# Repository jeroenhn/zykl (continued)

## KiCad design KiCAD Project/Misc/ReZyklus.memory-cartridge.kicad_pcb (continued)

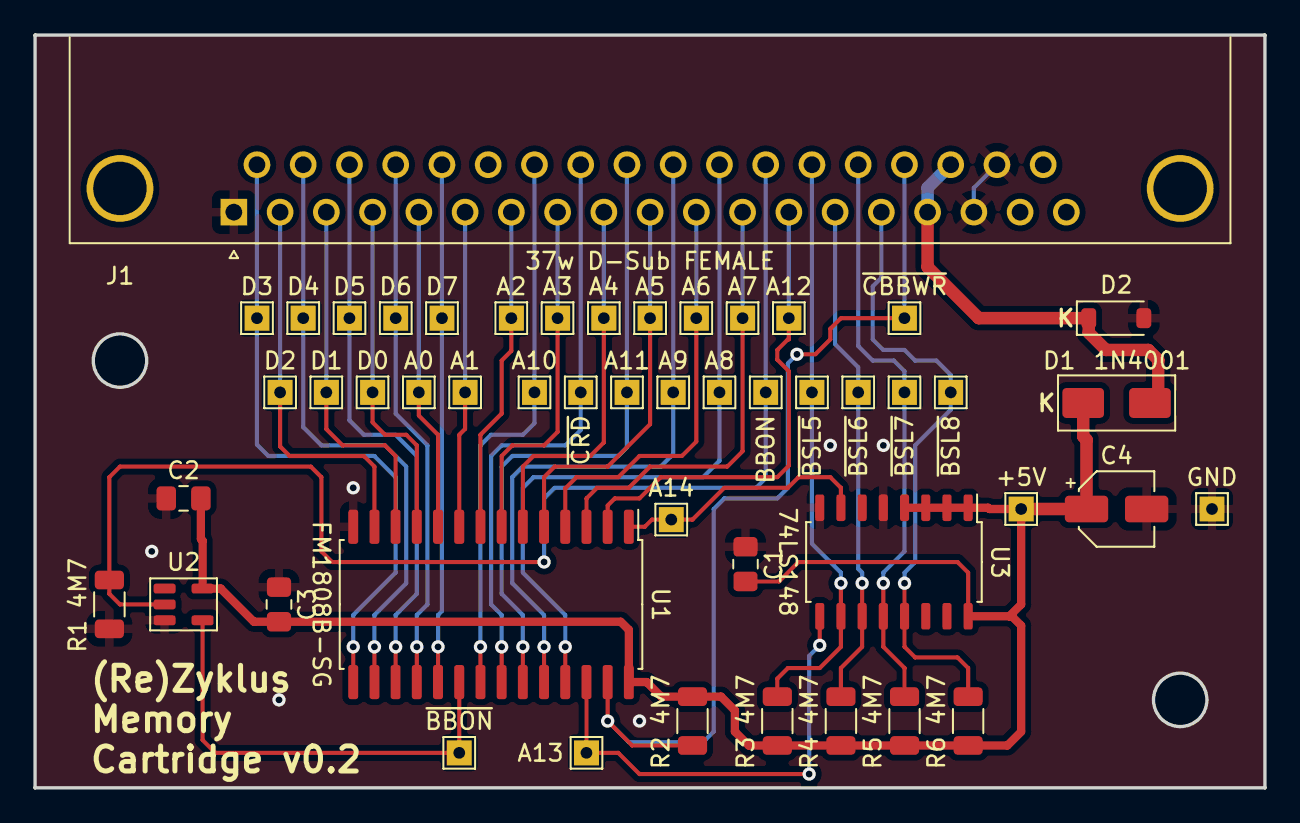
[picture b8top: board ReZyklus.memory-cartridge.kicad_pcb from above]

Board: 2 copper layers, 73.7 x 45.1 mm, 49 parts (0 on the bottom side), 34 nets.

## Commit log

2025-12-29 initial upload
2026-01-31 Revise README.md for clarity and contributions
    Updated the README.md to reflect project contributions and details.
2026-01-31 Update README.md with project details and credits
2026-02-01 Update README with blog and Discord links
    Added links to project blog and Discourse server for community engagement.
2026-02-06 update (#1)
2026-02-06 Revise README with team acknowledgements and updates
    Added team members to the project acknowledgements and updated the README structure.
2026-02-06 Update README.md with project details and acknowledgements
2026-02-07 Update README with V2 project details and acknowledgments
    Added information about the V2 successor project and acknowledged Jeroen's contribution.
2026-02-07 Update README with V2 project details and acknowledgments (#2)
    Added information about the V2 successor project and acknowledged Jeroen's contribution.
2026-02-07 Update README with project details and resources
    Added a detailed explanation of the Zyklus MPS-1 and its components, including links to resources and acknowledgments for contributors.
2026-02-07 Update README with project details and acknowledgements
2026-02-07 Revise README with project details and acknowledgments
    Updated project description, team acknowledgments, and licensing information in README.md.
2026-02-07 Added manual
